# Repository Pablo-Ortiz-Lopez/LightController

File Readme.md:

# LightController

The LightController is a versatile device designed to provide remote control for up to three dimmer units. This README provides a brief overview of the project's status and its available resources.

## Project Status

**Work In Progress (WIP)**

The LightController project is currently a work in progress. As such, I am actively developing and refining its features, firmware, and hardware components. While the project is in its early stages, I recommend patience until a stable working prototype is achieved.

## Features

The LightController aims to offer the following features once it reaches a stable state:

- **Remote Dimmer Control**: Control up to three dimmer units remotely, allowing you to adjust the lighting in your space effortlessly.

## Resources

To support the development and utilization of the LightController, I provide the following resources:

- **Firmware**: The firmware for the LightController is available as a PlatformIO project. This firmware will enable the remote control of dimmer units once it is fully developed.

- **Electronics**: The electronic design of the LightController can be found in the KiCad project files. These files enable you to understand and customize the hardware aspects of the device to fit your specific needs.

## Getting Involved

I welcome contributors who are interested in helping me refine and complete the LightController project. If you have ideas, suggestions, or code improvements, please feel free to contribute. Together, we can make this project a valuable addition to the world of remote lighting control.

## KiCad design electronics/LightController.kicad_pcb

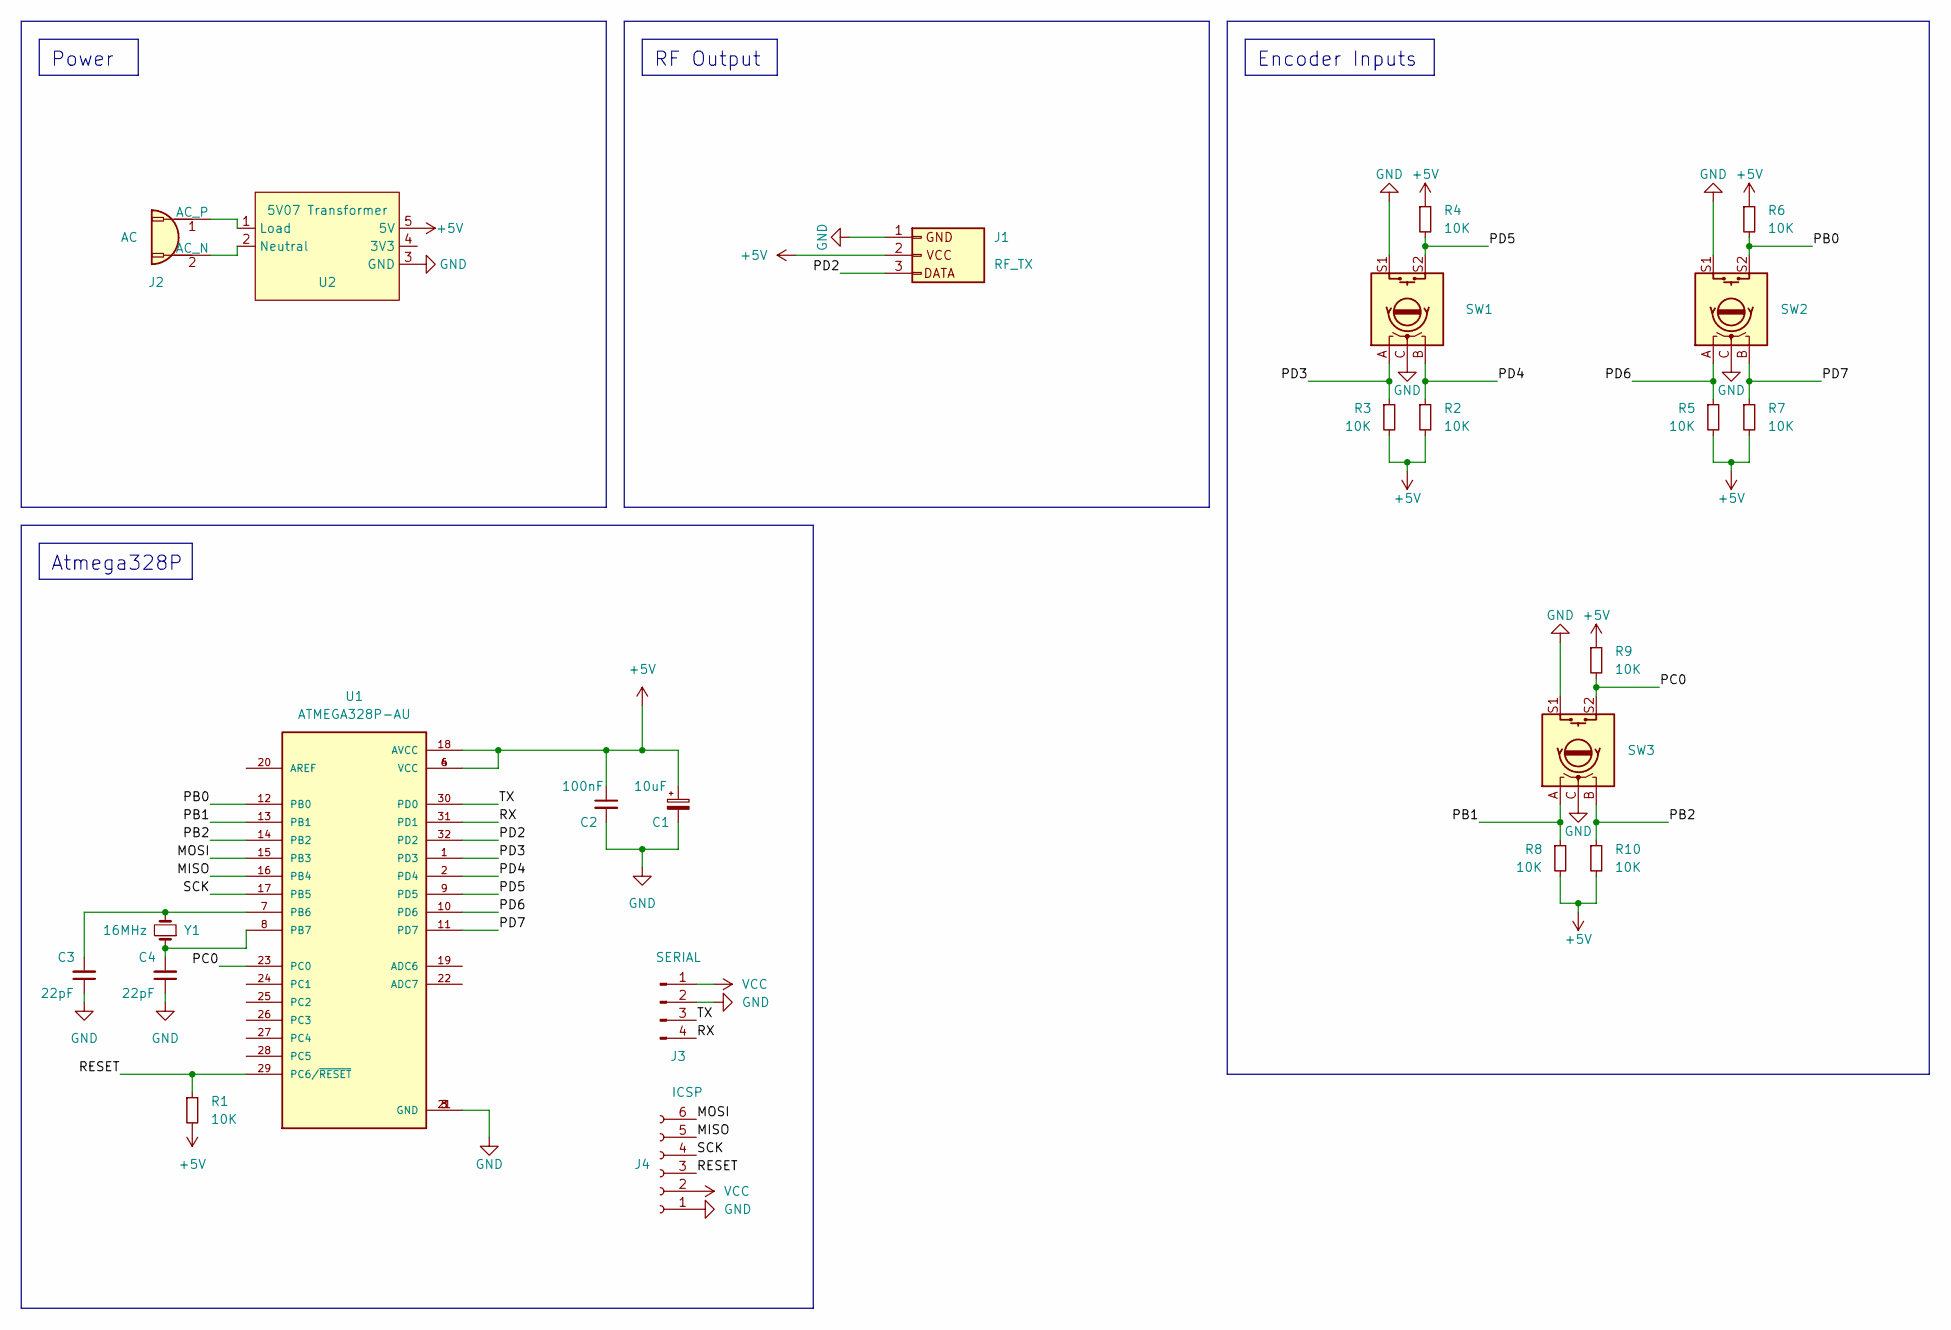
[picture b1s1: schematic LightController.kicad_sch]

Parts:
C1: 10uF; CP_Elec_6.3x4.9
C2: 100nF; C_1210_3225Metric_Pad1.33x2.70mm_HandSolder
C3, C4: 22pF; C_0805_2012Metric_Pad1.18x1.45mm_HandSolder
J1: RF_TX; RF ASK Emitter
J2: AC; Terminal_KF128-2P
J3: SERIAL; PinHeader_1x04_P2.54mm_Vertical
J4: ICSP; JST_PH_B6B-PH-K_1x06_P2.00mm_Vertical
R1, R2, R3, R4, R5, R6, R7, R8, R9, R10: 10K; R_1206_3216Metric_Pad1.30x1.75mm_HandSolder
SW1, SW2, SW3: RotaryEncoder_Switch; RotaryEncoder_Alps_EC11E-Switch_Vertical_H20mm
U1: ATMEGA328P-AU; Atmega328p-TQFP
U2: 5V07 Transformer; 5V07
Y1: 16MHz; Crystal_HC49-4H_Vertical

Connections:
+5V: C1.1, C2.1, J1.2 (VCC), R1.2, R2.2, R3.2, R4.1, R5.2, R6.1, R7.2, R8.2, R9.1, R10.2, U1.4 (VCC), U1.6 (VCC), U1.18 (AVCC), U2.5 (5V)
/MISO: J4.5, U1.16 (PB4)
/MOSI: J4.6, U1.15 (PB3)
/PB0: R6.2, SW2.S2, U1.12 (PB0)
/PB1: R8.1, SW3.A, U1.13 (PB1)
/PB2: R10.1, SW3.B, U1.14 (PB2)
/PC0: R9.2, SW3.S2, U1.23 (PC0)
/PD2: J1.3 (DATA), U1.32 (PD2)
/PD3: R3.1, SW1.A, U1.1 (PD3)
/PD4: R2.1, SW1.B, U1.2 (PD4)
/PD5: R4.2, SW1.S2, U1.9 (PD5)
/PD6: R5.1, SW2.A, U1.10 (PD6)
/PD7: R7.1, SW2.B, U1.11 (PD7)
/RESET: J4.3, R1.1, U1.29 (PC6/~RESET)
/RX: J3.4, U1.31 (PD1)
/SCK: J4.4, U1.17 (PB5)
/TX: J3.3, U1.30 (PD0)
GND: C1.2, C2.2, C3.1, C4.1, J1.1 (GND), J3.2, J4.1, SW1.C, SW1.S1, SW2.C, SW2.S1, SW3.C, SW3.S1, U1.3 (GND), U1.5 (GND), U1.21 (GND), U2.3 (GND)
unnamed: J2.2 (AC_N), U2.2 (Neutral)
unnamed: J2.1 (AC_P), U2.1 (Load)
unnamed: C3.2, U1.7 (PB6), Y1.2
unnamed: C4.2, U1.8 (PB7), Y1.1
VCC: J3.1, J4.2

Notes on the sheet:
Atmega328P
Encoder Inputs
Power
RF Output

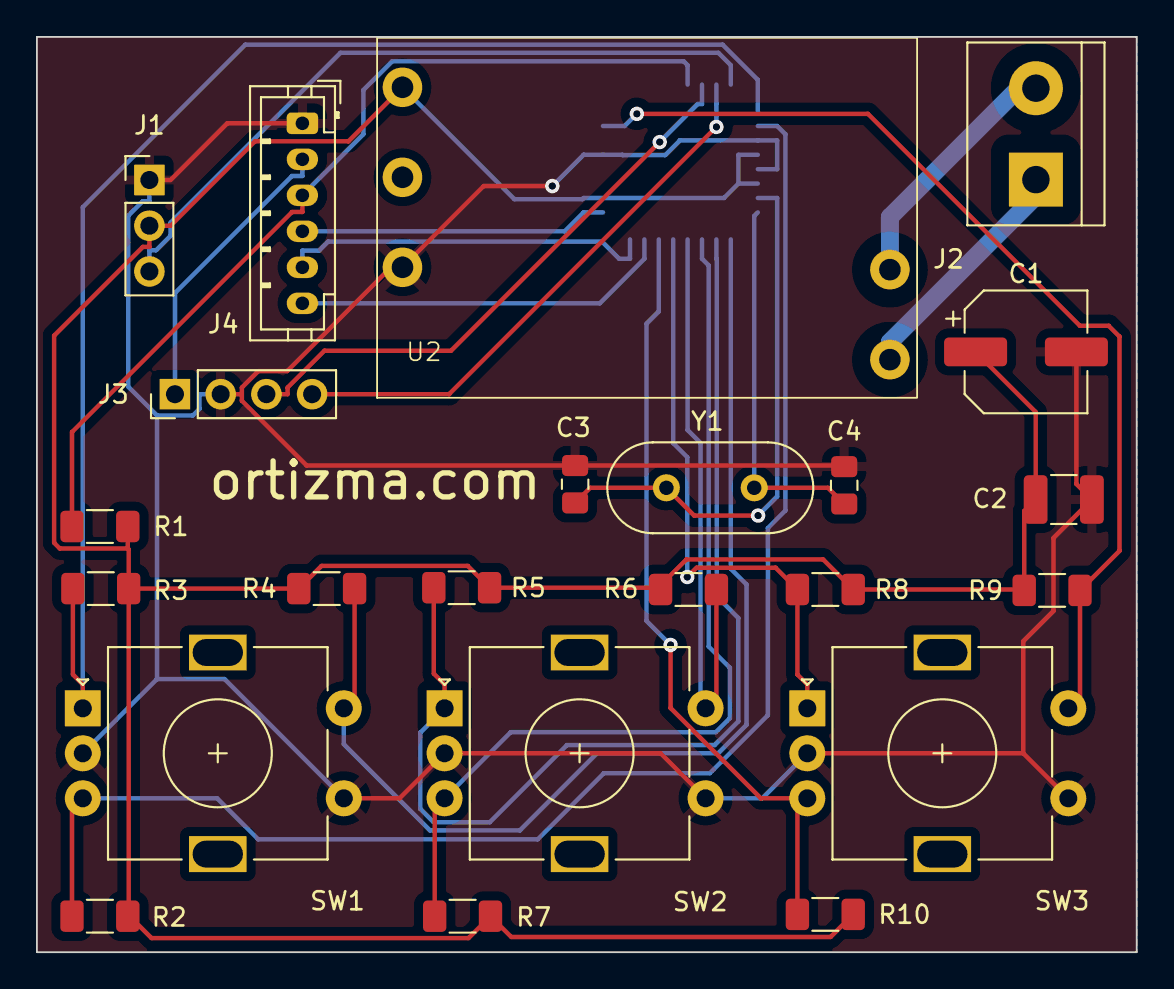
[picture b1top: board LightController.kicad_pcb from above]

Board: 2 copper layers, 61.1 x 50.9 mm, 24 parts (1 on the bottom side), 23 nets.

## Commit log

2023-10-22 Add readme & structure
